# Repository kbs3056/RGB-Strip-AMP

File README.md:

# RGB-Strip-AMP

12V RGB LED strip amplifier is used to reduce the voltage drop in long LED strips.

### Output
3x1.5A, 2.5-5m 5050 LED.

Amplifier needs an external 12V and GND supply lines.
All LED strips connected in one circuit should be powered by the same power supply. (Input 12V and Output 12V rails are connected.)

See wiring diagram. https://github.com/kbs3056/RGB-Strip-AMP/blob/main/wiring_diagram.pdf

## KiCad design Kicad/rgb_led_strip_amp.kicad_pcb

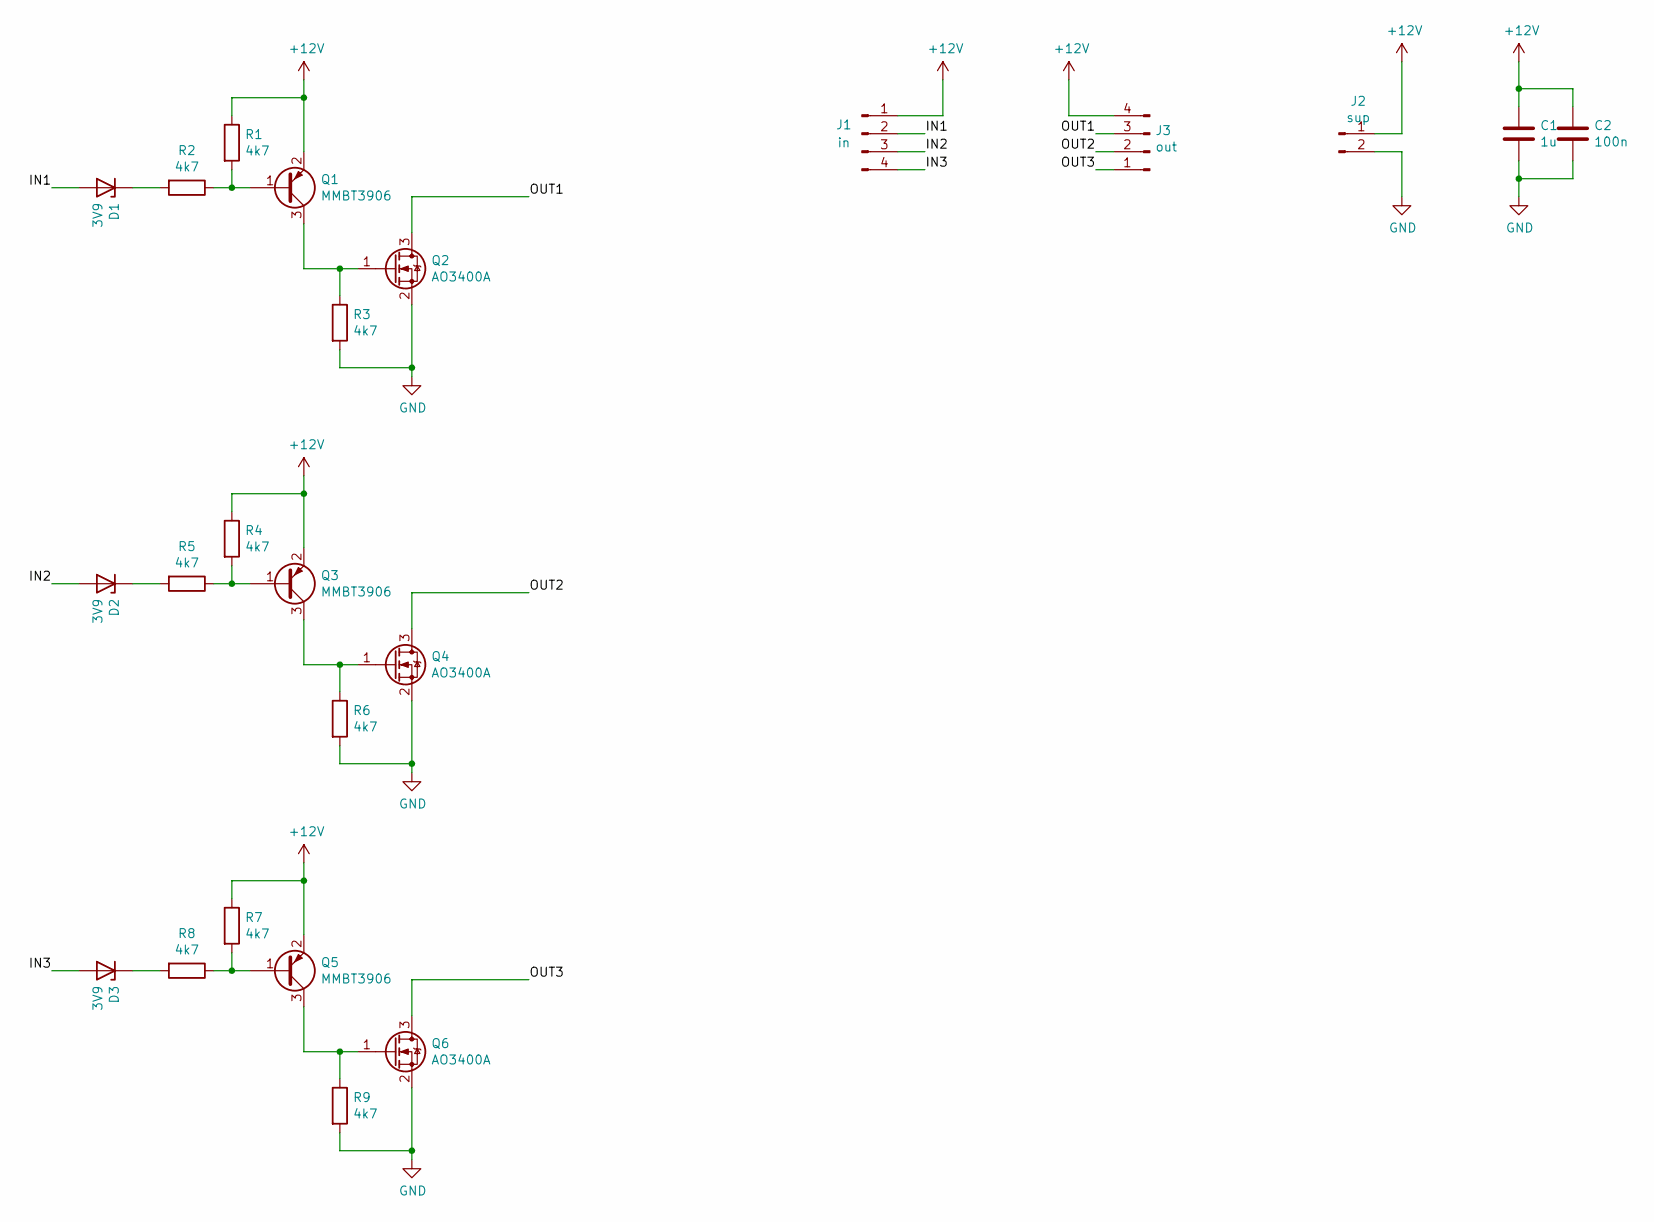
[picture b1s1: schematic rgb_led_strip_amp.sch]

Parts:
C1: 1u; C_0805_2012Metric
C2: 100n; C_0805_2012Metric
D1, D2, D3: 3V9; D_SOT-23_ANK
J1: in; solderpad_4_copy
J2: sup; solderpad_2
J3: out; solderpad_4_copy
Q1, Q3, Q5: MMBT3906; SOT-23
Q2, Q4, Q6: AO3400A; SOT-23
R1, R2, R3, R4, R5, R6, R7, R8, R9: 4k7; R_1206_3216Metric

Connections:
+12V: C1.1, C2.1, J1.1, J2.1, J3.4, Q1.2 (E), Q3.2 (E), Q5.2 (E), R1.1, R4.1, R7.1
/IN1: D1.2 (A), J1.2
/IN2: D2.2 (A), J1.3
/IN3: D3.2 (A), J1.4
/OUT1: J3.3, Q2.3 (D)
/OUT2: J3.2, Q4.3 (D)
/OUT3: J3.1, Q6.3 (D)
GND: C1.2, C2.2, J2.2, Q2.2 (S), Q4.2 (S), Q6.2 (S), R3.2, R6.2, R9.2
unnamed: D1.1 (K), R2.2
unnamed: D2.1 (K), R5.2
unnamed: D3.1 (K), R8.2
unnamed: Q1.1 (B), R1.2, R2.1
unnamed: Q1.3 (C), Q2.1 (G), R3.1
unnamed: Q3.1 (B), R4.2, R5.1
unnamed: Q3.3 (C), Q4.1 (G), R6.1
unnamed: Q5.1 (B), R7.2, R8.1
unnamed: Q5.3 (C), Q6.1 (G), R9.1

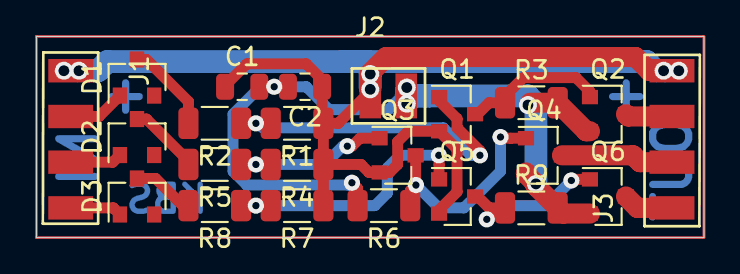
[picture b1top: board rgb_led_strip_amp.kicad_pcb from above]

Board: 2 copper layers, 37.1 x 11.2 mm, 23 parts (0 on the bottom side), 17 nets.

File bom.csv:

Reference, Quantity, Value, Footprint, Datasheet
C1 ,1,1u,Capacitor_SMD:C_0805_2012Metric,~
C2 ,1,100n,Capacitor_SMD:C_0805_2012Metric,~
D1 D2 D3 ,3,3V9,Diode_SMD:D_SOT-23_ANK,~
Q1 Q3 Q5 ,3,MMBT3906,Package_TO_SOT_SMD:SOT-23,https://www.onsemi.com/pub/Collateral/2N3906-D.PDF
Q2 Q4 Q6 ,3,AO3400A,Package_TO_SOT_SMD:SOT-23,http://www.aosmd.com/pdfs/datasheet/AO3400A.pdf
R1 R2 R3 R4 R5 R6 R7 R8 R9 ,9,4k7,Resistor_SMD:R_1206_3216Metric,~
